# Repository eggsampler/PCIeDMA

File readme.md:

# PCIeDMA

Open source Artix-7 FPGA designed to be used with [PCILeech](https://github.com/ufrisk/pcileech/).

For schematic/layout/assembly/pcb diagrams, please see the [outputs](outputs/) folder.

## Overview

Initial design was based on a combination of the [LambdaConcept PCIe Screamer Squirrel](https://shop.lambdaconcept.com/home/50-screamer-pcie-squirrel.html) and the [Enigma-X1 LeetDMA](https://enigma-x1.com/store/product/23-leetdma-incl-custom-fw/).

PCIexpress layout is based on [lucanastasio/PCIexpress-KiCad](https://github.com/lucanastasio/PCIexpress-KiCad) PCIexpress_x4_low.

Initially will try to keep the board as a 6-layer PCB using the [JLC3313 6-Layer Impedance Control Stackup](https://cart.jlcpcb.com/impedance), layer stackup plan would be Signal/Ground/Power/Power/Ground/Signal, with the outside signal layers also having a ground pour. PCIe and USB3 SS traces would be impedance matched (and length matched as necessary) on top and bottom layers as coplanar waveguides for each pair.

There are two on-board USB-C ports, one for JTAG debugging/programming of the FPGA/flash, the other as a usb superspeed link for DMA access. The board is also designed such that it can be powered and programmed/tested from the JTAG USB connector, without needing to be plugged into a PCIe slot.

## Progress 

From a high level perspective, the board is largely complete. It does, however, need to be checked before first batch ordered. The following is a rough list of what needs to be reviewed, and any input is welcome from knowledgeable parties.

* [ ] Schematic Review
  * [ ] Part Selection
  * [ ] BOM Check
  * [ ] Connectivity

* [ ] PCB Review
  * [ ] Placement
  * [ ] Footprints
  * [ ] Routing
  * [ ] Impedance

Once board is finalised, the software side needs to be started integrating with PCILeech. Specifically, [PCILeech FPGA](https://github.com/ufrisk/pcileech-fpga)

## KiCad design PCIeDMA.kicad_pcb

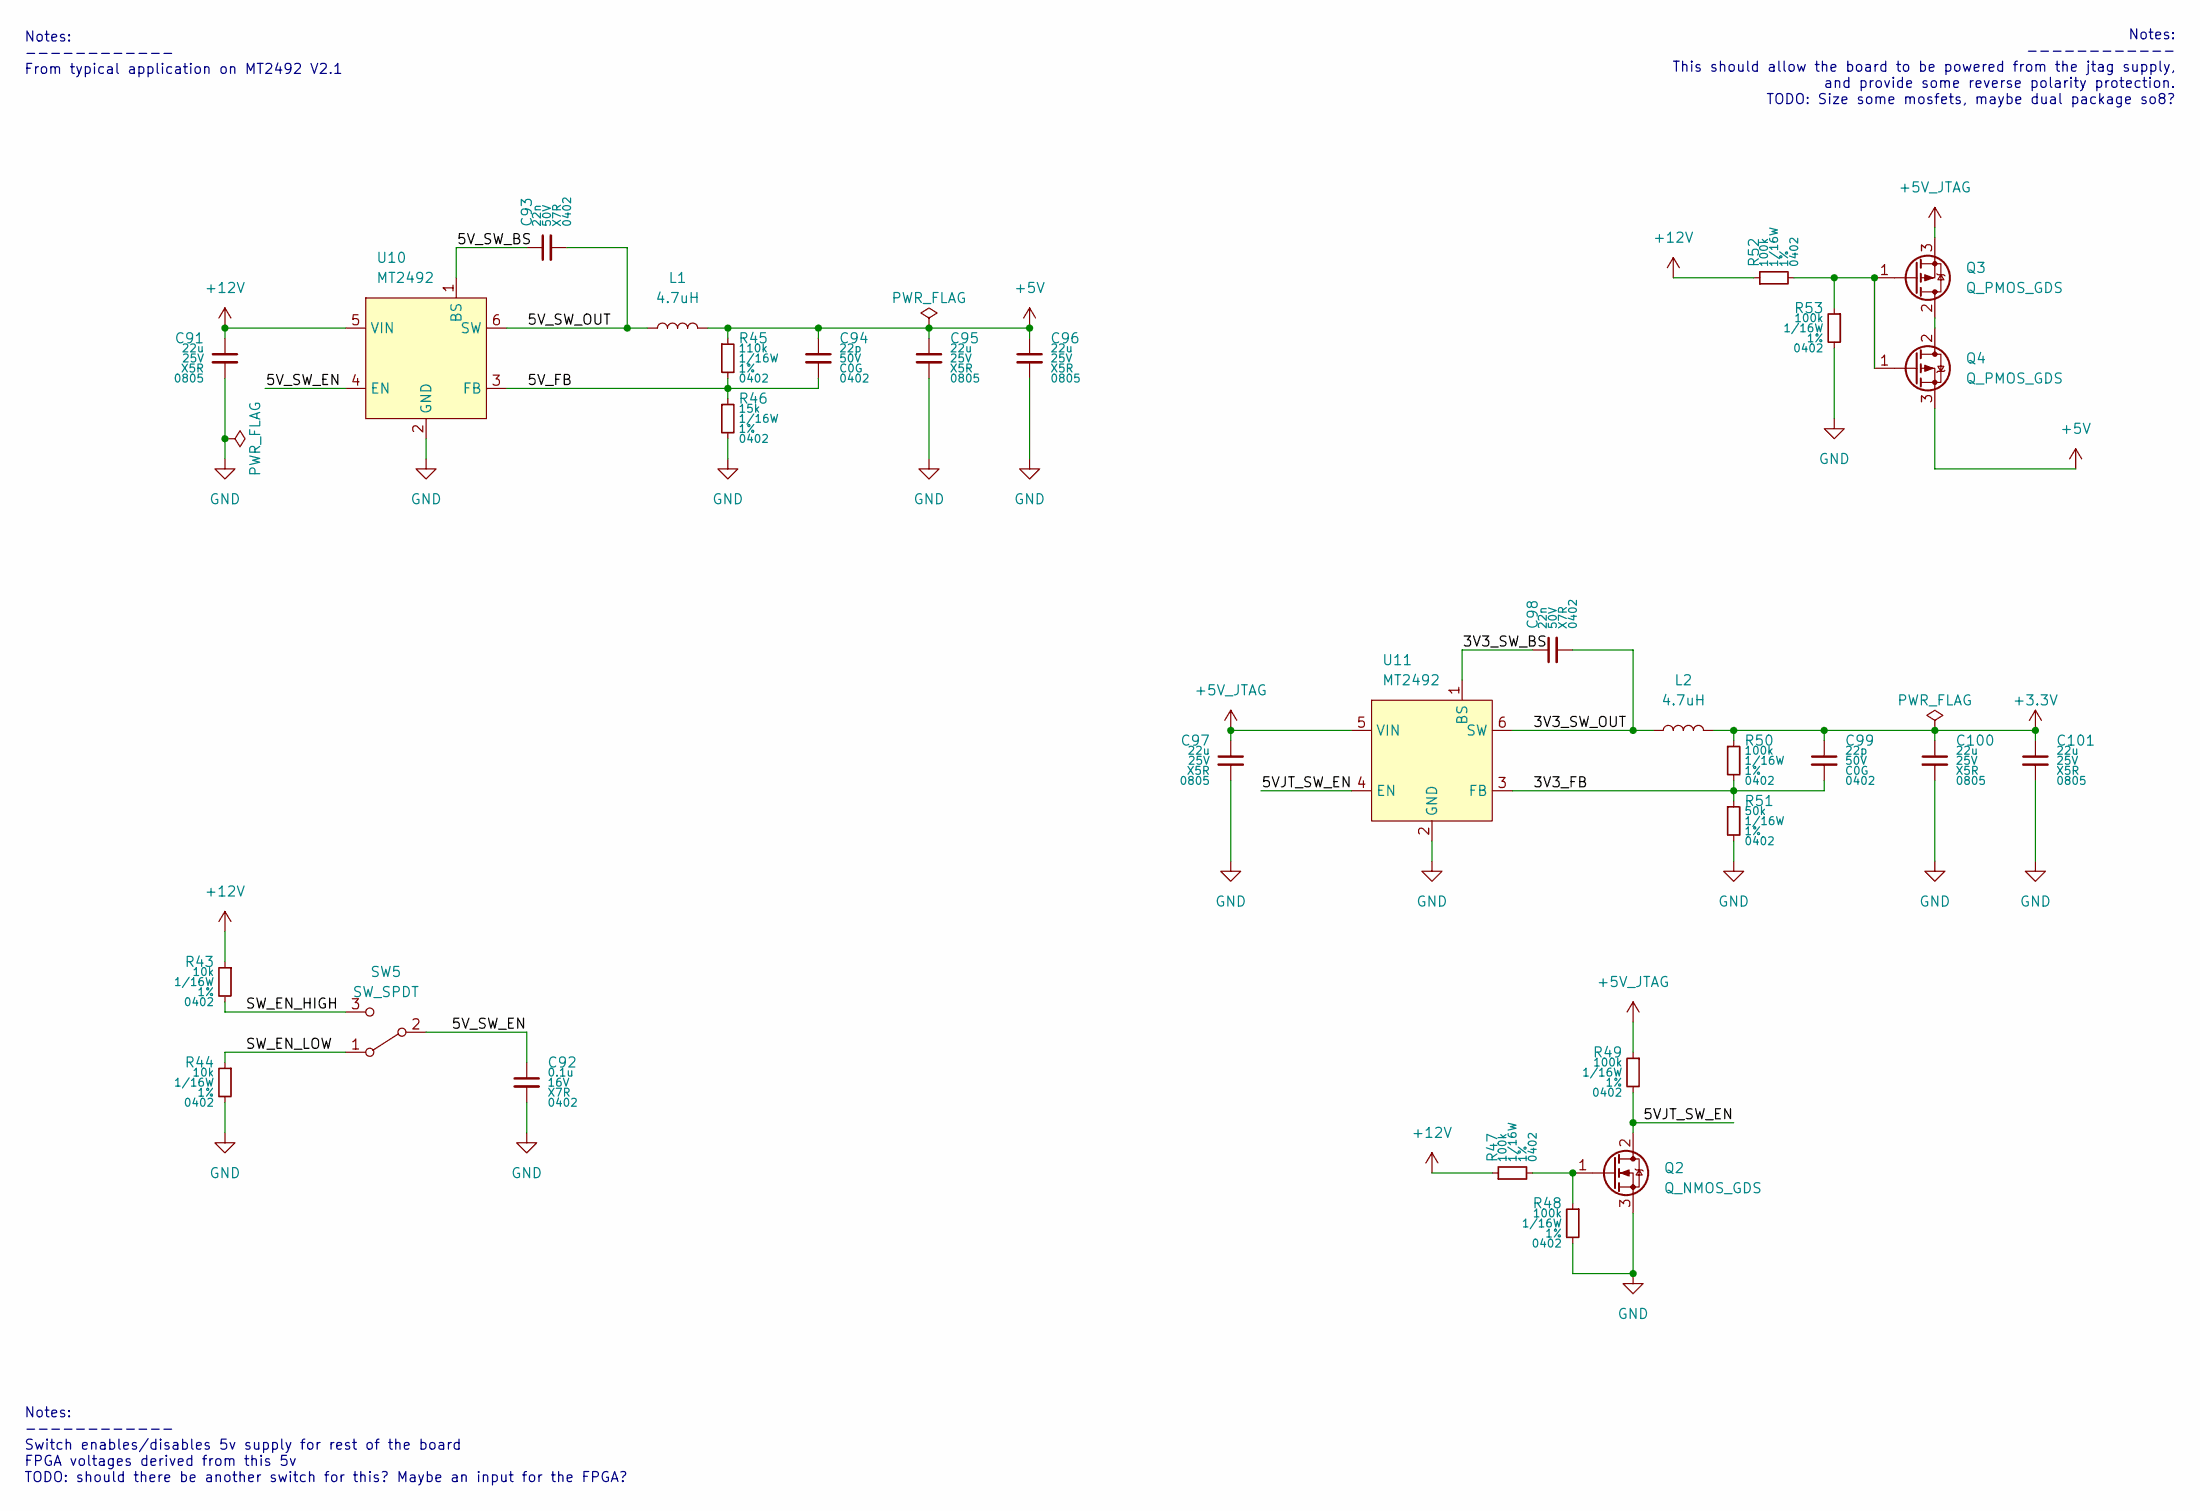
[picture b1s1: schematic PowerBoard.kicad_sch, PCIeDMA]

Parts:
C91, C95, C96, C97, C100, C101: 22u; C_0805_2012Metric; Rating 25V
C92: 0.1u; C_0402_1005Metric; Rating 16V
C93, C98: 22n; C_0402_1005Metric; Rating 50V
C94, C99: 22p; C_0402_1005Metric; Rating 50V
L1, L2: 4.7uH; L_Vishay_IHLP-2020
Q2: Q_NMOS_GDS; SOT-23
Q3, Q4: Q_PMOS_GDS; SOT-23
R43, R44: 10k; R_0402_1005Metric; Rating 1/16W; Tolerance 1%
R45: 110k; R_0402_1005Metric; Rating 1/16W; Tolerance 1%
R46: 15k; R_0402_1005Metric; Rating 1/16W; Tolerance 1%
R47, R48, R49, R50, R52, R53: 100k; R_0402_1005Metric; Rating 1/16W; Tolerance 1%
R51: 50k; R_0402_1005Metric; Rating 1/16W; Tolerance 1%
SW5: SW_SPDT; ST-0-102-C03-N003-RS
U10, U11: MT2492; SOT-23-6

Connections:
+3.3V: C99.1, C100.1, C101.1, L2.2, R50.1; also elsewhere on the board
+5V: C94.1, C95.1, C96.1, L1.2, Q4.3 (S), R45.1; also elsewhere on the board
+5V_JTAG: C97.1, Q3.3 (S), R49.1, U11.5 (VIN); also elsewhere on the board
+12V: C91.1, R43.1, R47.1, R52.1, U10.5 (VIN); also elsewhere on the board
/Board Power/3V3_FB: C99.2, R50.2, R51.1, U11.3 (FB)
/Board Power/3V3_SW_BS: C98.1, U11.1 (BS)
/Board Power/3V3_SW_OUT: C98.2, L2.1, U11.6 (SW)
/Board Power/5VJT_SW_EN: Q2.2 (D), R49.2, U11.4 (EN)
/Board Power/5V_FB: C94.2, R45.2, R46.1, U10.3 (FB)
/Board Power/5V_SW_BS: C93.1, U10.1 (BS)
/Board Power/5V_SW_EN: C92.1, SW5.2 (B), U10.4 (EN)
/Board Power/5V_SW_OUT: C93.2, L1.1, U10.6 (SW)
/Board Power/SW_EN_HIGH: R43.2, SW5.3 (C)
/Board Power/SW_EN_LOW: R44.1, SW5.1 (A)
GND: C91.2, C92.2, C95.2, C96.2, C97.2, C100.2, C101.2, Q2.3 (S), R44.2, R46.2, R48.2, R51.2, R53.2, U10.2 (GND), U11.2 (GND); also elsewhere on the board
unnamed: Q2.1 (G), R47.2, R48.1
unnamed: Q3.2 (D), Q4.2 (D)
unnamed: Q3.1 (G), Q4.1 (G), R52.2, R53.1

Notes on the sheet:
Notes: ------------ From typical application on MT2492 V2.1
Notes: ------------ Switch enables/disables 5v supply for rest of the board FPGA voltages derived from this 5v TODO: should there be another switch for this? Maybe an input for the FPGA?
Notes: ------------ This should allow the board to be powered from the jtag supply, and provide some reverse polarity protection. TODO: Size some mosfets, maybe dual package so8?

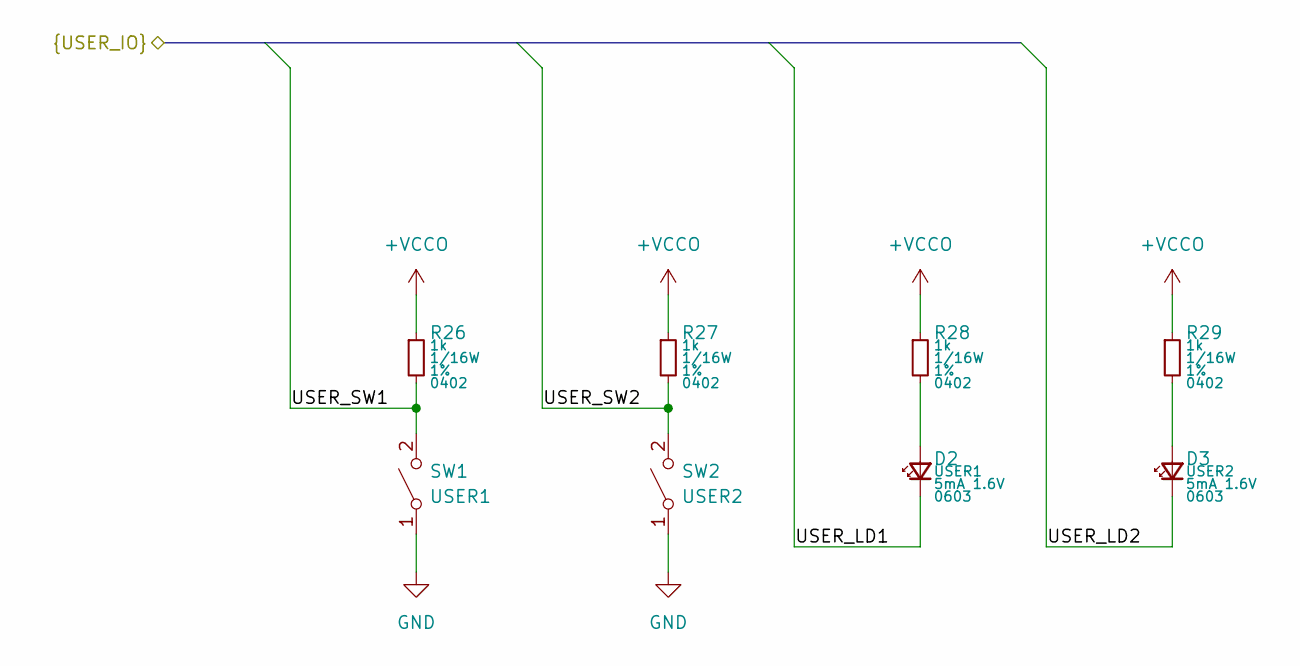
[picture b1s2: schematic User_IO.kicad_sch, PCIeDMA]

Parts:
D2: USER1; LED_0603_1608Metric; Rating 5mA 1.6V
D3: USER2; LED_0603_1608Metric; Rating 5mA 1.6V
R26, R27, R28, R29: 1k; R_0402_1005Metric; Rating 1/16W; Tolerance 1%
SW1: USER1; SW_SPST_B3U-1000P
SW2: USER2; SW_SPST_B3U-1000P

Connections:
+VCCO: R26.1, R27.1, R28.1, R29.1; also elsewhere on the board
/FPGA/USER_LD1: D2.1 (K); also elsewhere on the board
/FPGA/USER_LD2: D3.1 (K); also elsewhere on the board
/FPGA/USER_SW1: R26.2, SW1.2 (B); also elsewhere on the board
/FPGA/USER_SW2: R27.2, SW2.2 (B); also elsewhere on the board
GND: SW1.1 (A), SW2.1 (A); also elsewhere on the board
unnamed: D2.2 (A), R28.2
unnamed: D3.2 (A), R29.2

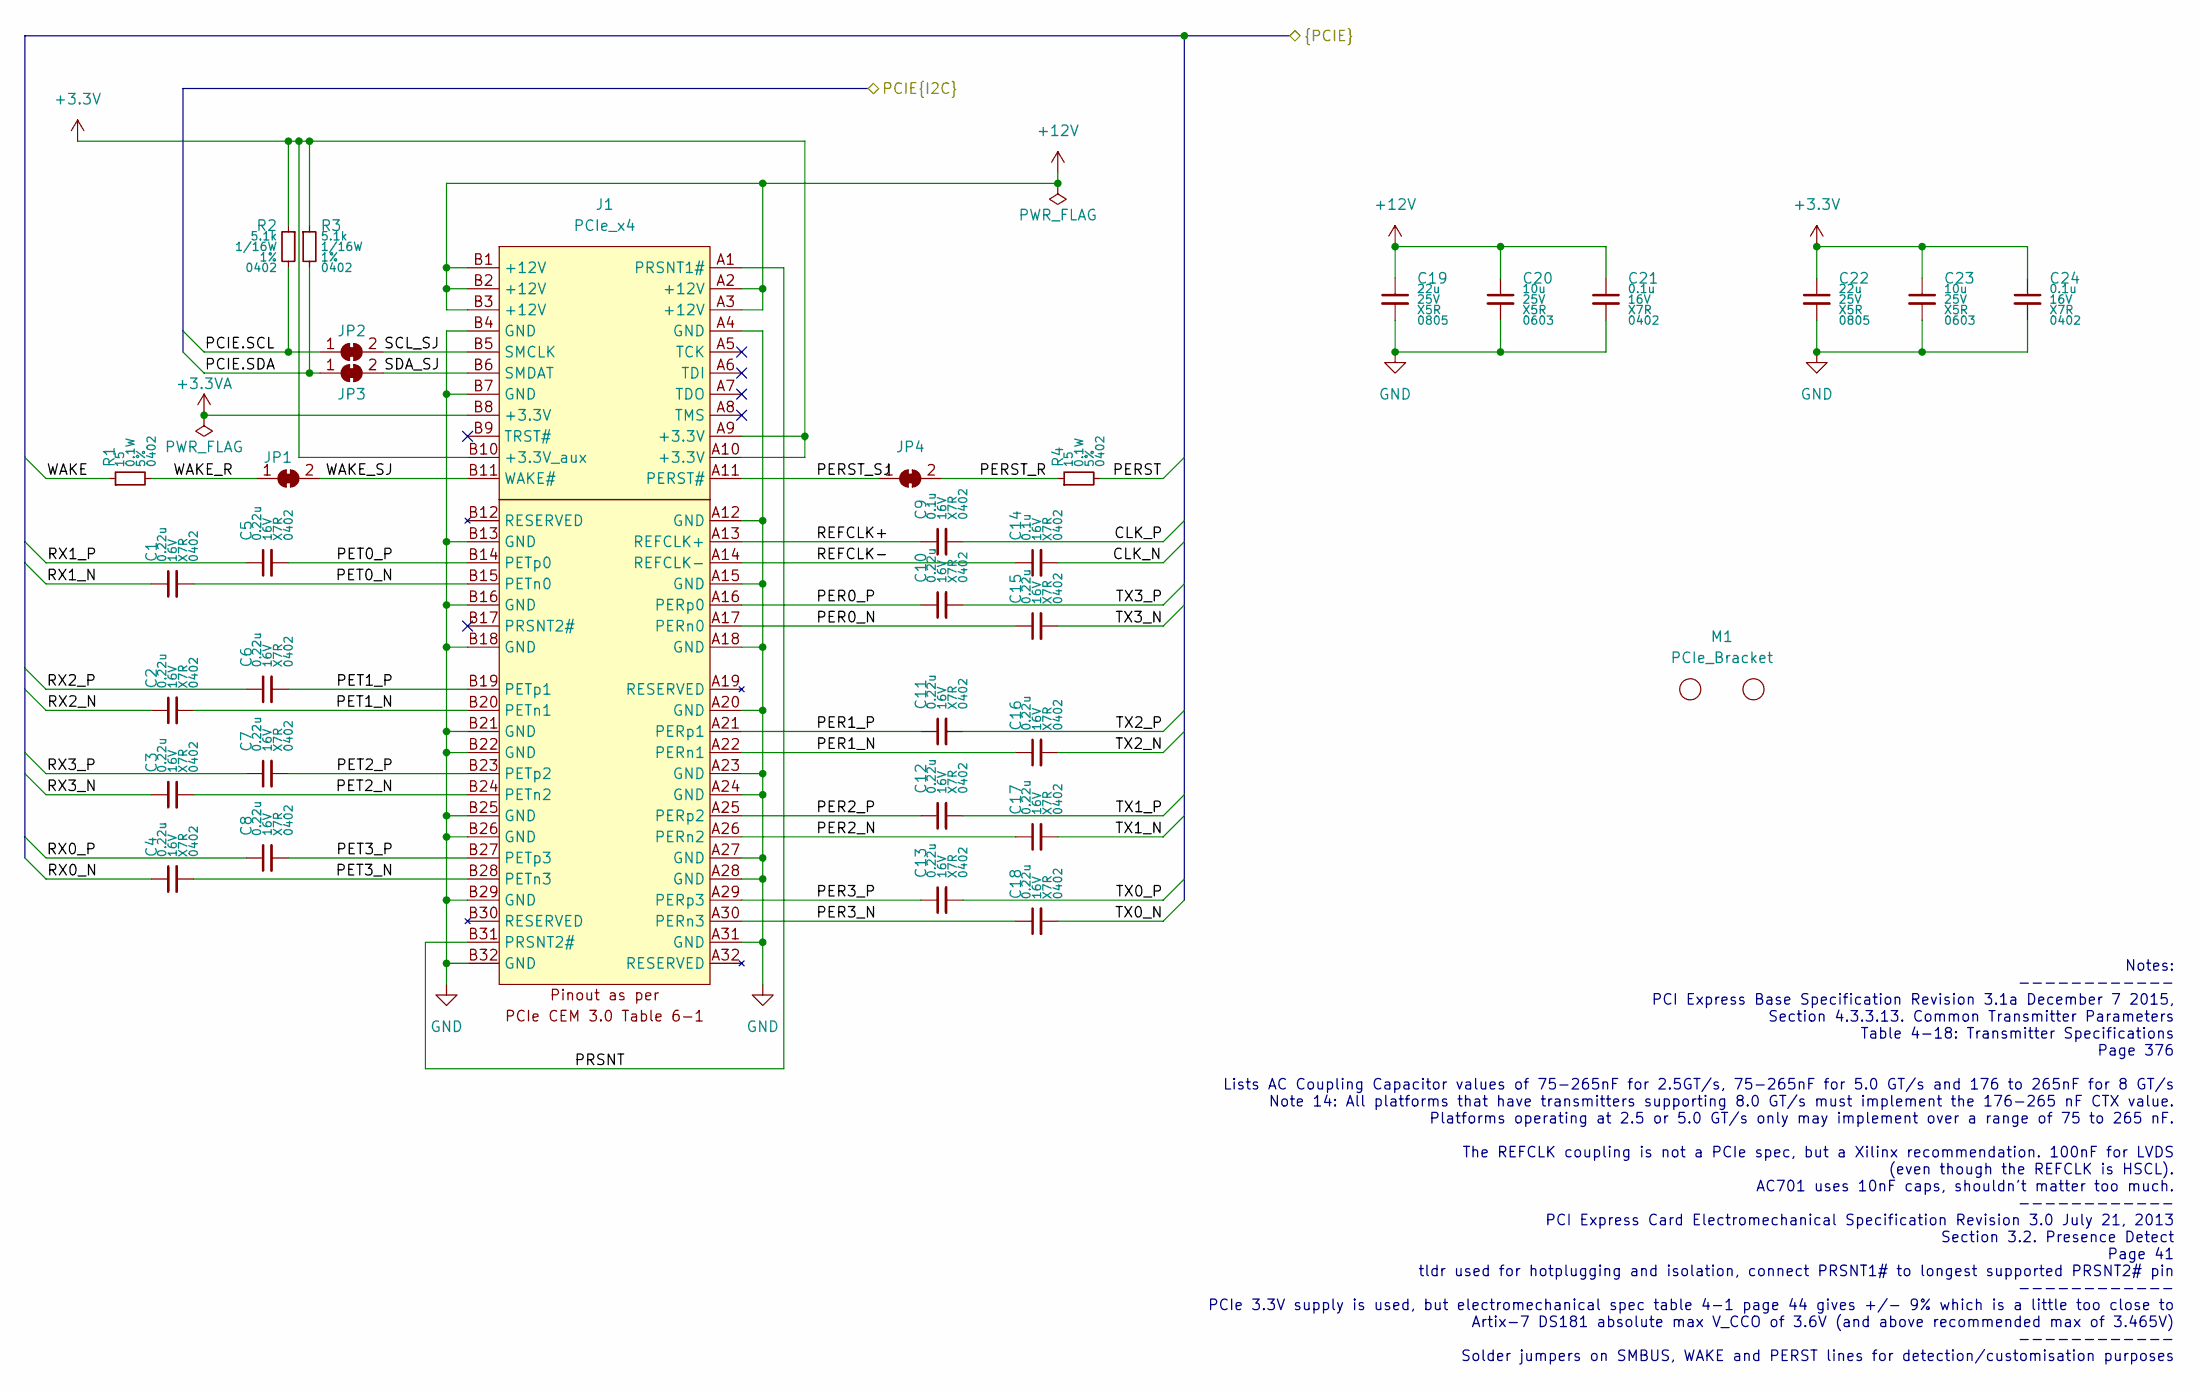
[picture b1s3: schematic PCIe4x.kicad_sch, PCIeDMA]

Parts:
C1, C2, C3, C4, C5, C6, C7, C8, C10, C11, C12, C13, C15, C16, C17, C18: 0.22u; C_0402_1005Metric; Rating 16V
C9, C14, C21, C24: 0.1u; C_0402_1005Metric; Rating 16V
C19, C22: 22u; C_0805_2012Metric; Rating 25V
C20, C23: 10u; C_0603_1608Metric; Rating 25V
J1: PCIe_x4; BUS_PCIexpress_x4
JP1, JP2, JP3, JP4: SolderJumper_2_Bridged; SolderJumper-2_P1.3mm_Bridged_RoundedPad1.0x1.5mm
M1: PCIe_Bracket
R1, R4: 15; R_0402_1005Metric; Rating 0.1W; Tolerance 5%
R2, R3: 5.1k; R_0402_1005Metric; Rating 1/16W; Tolerance 1%

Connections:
+3.3V: C22.1, C23.1, C24.1, J1.A9 (+3.3V), J1.A10 (+3.3V), J1.B10 (+3.3V_aux), R2.1, R3.1; also elsewhere on the board
+3.3VA: J1.B8 (+3.3V)
+12V: C19.1, C20.1, C21.1, J1.A2 (+12V), J1.A3 (+12V), J1.B1 (+12V), J1.B2 (+12V), J1.B3 (+12V); also elsewhere on the board
/FPGA/CLK_N: C14.2; also elsewhere on the board
/FPGA/CLK_P: C9.2; also elsewhere on the board
/FPGA/PCIE.SCL: JP2.1 (A), R2.2; also elsewhere on the board
/FPGA/PCIE.SDA: JP3.1 (A), R3.2; also elsewhere on the board
/FPGA/PERST: R4.2; also elsewhere on the board
/FPGA/RX0_N: C4.1; also elsewhere on the board
/FPGA/RX0_P: C8.1; also elsewhere on the board
/FPGA/RX1_N: C1.1; also elsewhere on the board
/FPGA/RX1_P: C5.1; also elsewhere on the board
/FPGA/RX2_N: C2.1; also elsewhere on the board
/FPGA/RX2_P: C6.1; also elsewhere on the board
/FPGA/RX3_N: C3.1; also elsewhere on the board
/FPGA/RX3_P: C7.1; also elsewhere on the board
/FPGA/TX0_N: C18.2; also elsewhere on the board
/FPGA/TX0_P: C13.2; also elsewhere on the board
/FPGA/TX1_N: C17.2; also elsewhere on the board
/FPGA/TX1_P: C12.2; also elsewhere on the board
/FPGA/TX2_N: C16.2; also elsewhere on the board
/FPGA/TX2_P: C11.2; also elsewhere on the board
/FPGA/TX3_N: C15.2; also elsewhere on the board
/FPGA/TX3_P: C10.2; also elsewhere on the board
/FPGA/WAKE: R1.1; also elsewhere on the board
/PCIe 4x/PER0_N: C15.1, J1.A17 (PERn0)
/PCIe 4x/PER0_P: C10.1, J1.A16 (PERp0)
/PCIe 4x/PER1_N: C16.1, J1.A22 (PERn1)
/PCIe 4x/PER1_P: C11.1, J1.A21 (PERp1)
/PCIe 4x/PER2_N: C17.1, J1.A26 (PERn2)
/PCIe 4x/PER2_P: C12.1, J1.A25 (PERp2)
/PCIe 4x/PER3_N: C18.1, J1.A30 (PERn3)
/PCIe 4x/PER3_P: C13.1, J1.A29 (PERp3)
/PCIe 4x/PERST_R: JP4.2 (B), R4.1
/PCIe 4x/PERST_SJ: J1.A11 (PERST#), JP4.1 (A)
/PCIe 4x/PET0_N: C1.2, J1.B15 (PETn0)
/PCIe 4x/PET0_P: C5.2, J1.B14 (PETp0)
/PCIe 4x/PET1_N: C2.2, J1.B20 (PETn1)
/PCIe 4x/PET1_P: C6.2, J1.B19 (PETp1)
/PCIe 4x/PET2_N: C3.2, J1.B24 (PETn2)
/PCIe 4x/PET2_P: C7.2, J1.B23 (PETp2)
/PCIe 4x/PET3_N: C4.2, J1.B28 (PETn3)
/PCIe 4x/PET3_P: C8.2, J1.B27 (PETp3)
/PCIe 4x/PRSNT: J1.A1 (PRSNT1#), J1.B31 (PRSNT2#)
/PCIe 4x/REFCLK+: C9.1, J1.A13 (REFCLK+)
/PCIe 4x/REFCLK-: C14.1, J1.A14 (REFCLK-)
/PCIe 4x/SCL_SJ: J1.B5 (SMCLK), JP2.2 (B)
/PCIe 4x/SDA_SJ: J1.B6 (SMDAT), JP3.2 (B)
/PCIe 4x/WAKE_R: JP1.1 (A), R1.2
/PCIe 4x/WAKE_SJ: J1.B11 (WAKE#), JP1.2 (B)
GND: C19.2, C20.2, C21.2, C22.2, C23.2, C24.2, J1.A4 (GND), J1.A12 (GND), J1.A15 (GND), J1.A18 (GND), J1.A20 (GND), J1.A23 (GND), J1.A24 (GND), J1.A27 (GND), J1.A28 (GND), J1.A31 (GND), J1.B4 (GND), J1.B7 (GND), J1.B13 (GND), J1.B16 (GND), J1.B18 (GND), J1.B21 (GND), J1.B22 (GND), J1.B25 (GND), J1.B26 (GND), J1.B29 (GND), J1.B32 (GND); also elsewhere on the board

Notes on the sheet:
Notes: ------------ PCI Express Base Specification Revision 3.1a December 7 2015, Section 4.3.3.13. Common Transmitter Parameters Table 4-18: Transmitter Specifications Page 376 Lists AC Coupling Capacitor values of 75-265nF for 2.5GT/s, 75-265nF for 5.0 GT/s and 176 to 265nF for 8 GT/s Note 14: Al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

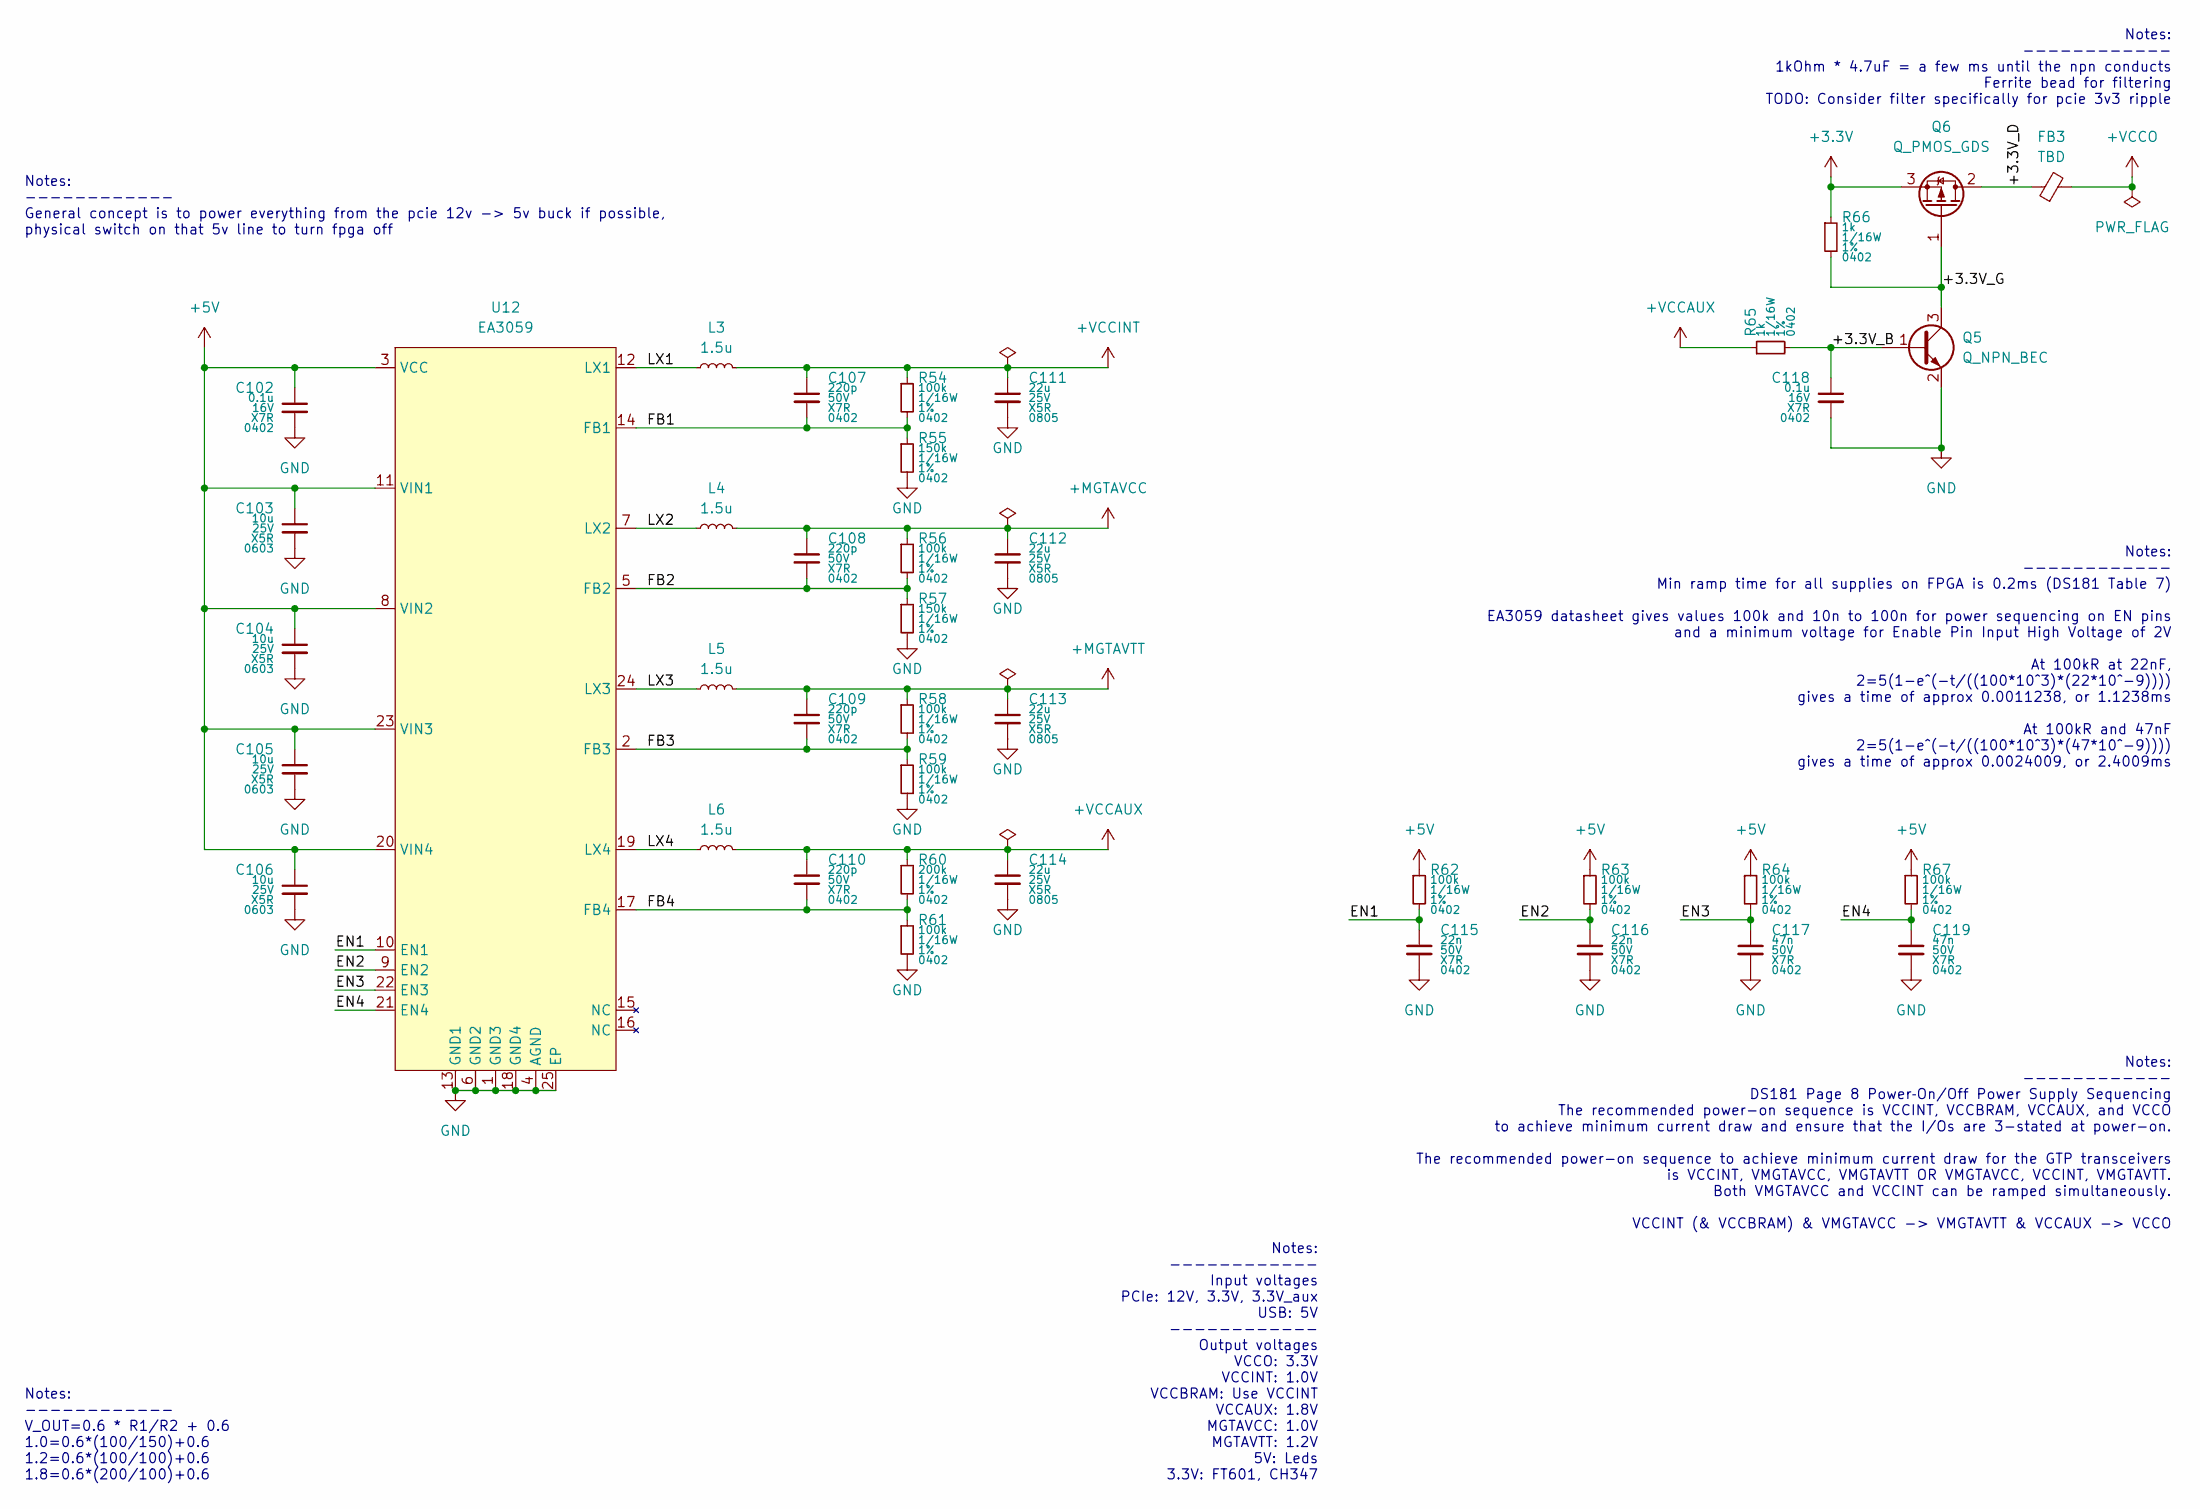
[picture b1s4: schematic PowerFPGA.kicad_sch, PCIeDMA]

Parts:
C102, C118: 0.1u; C_0402_1005Metric; Rating 16V
C103, C104, C105, C106: 10u; C_0603_1608Metric; Rating 25V
C107, C108, C109, C110: 220p; C_0402_1005Metric; Rating 50V
C111, C112, C113, C114: 22u; C_0805_2012Metric; Rating 25V
C115, C116: 22n; C_0402_1005Metric; Rating 50V
C117, C119: 47n; C_0402_1005Metric; Rating 50V
FB3: TBD; L_0805_2012Metric
L3, L4, L5, L6: 1.5u; L_Abracon_ASPI-3012S
Q5: Q_NPN_BEC; SOT-23
Q6: Q_PMOS_GDS; SOT-23
R54, R56, R58, R59, R61, R62, R63, R64, R67: 100k; R_0402_1005Metric; Rating 1/16W; Tolerance 1%
R55, R57: 150k; R_0402_1005Metric; Rating 1/16W; Tolerance 1%
R60: 200k; R_0402_1005Metric; Rating 1/16W; Tolerance 1%
R65, R66: 1k; R_0402_1005Metric; Rating 1/16W; Tolerance 1%
U12: EA3059; QFN-24-1EP_4x4mm_P0.5mm_EP2.6x2.6mm

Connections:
+3.3V: Q6.3 (S), R66.1; also elsewhere on the board
+5V: C102.1, C103.1, C104.1, C105.1, C106.1, R62.1, R63.1, R64.1, R67.1, U12.3 (VCC), U12.8 (VIN2), U12.11 (VIN1), U12.20 (VIN4), U12.23 (VIN3); also elsewhere on the board
+MGTAVCC: C108.1, C112.1, L4.2, R56.1; also elsewhere on the board
+MGTAVTT: C109.1, C113.1, L5.2, R58.1; also elsewhere on the board
+VCCAUX: C110.1, C114.1, L6.2, R60.1, R65.1; also elsewhere on the board
+VCCINT: C107.1, C111.1, L3.2, R54.1; also elsewhere on the board
+VCCO: FB3.2; also elsewhere on the board
/FPGA Power/+3.3V_B: C118.1, Q5.1 (B), R65.2
/FPGA Power/+3.3V_D: FB3.1, Q6.2 (D)
/FPGA Power/+3.3V_G: Q5.3 (C), Q6.1 (G), R66.2
/FPGA Power/EN1: C115.1, R62.2, U12.10 (EN1)
/FPGA Power/EN2: C116.1, R63.2, U12.9 (EN2)
/FPGA Power/EN3: C117.1, R64.2, U12.22 (EN3)
/FPGA Power/EN4: C119.1, R67.2, U12.21 (EN4)
/FPGA Power/FB1: C107.2, R54.2, R55.1, U12.14 (FB1)
/FPGA Power/FB2: C108.2, R56.2, R57.1, U12.5 (FB2)
/FPGA Power/FB3: C109.2, R58.2, R59.1, U12.2 (FB3)
/FPGA Power/FB4: C110.2, R60.2, R61.1, U12.17 (FB4)
/FPGA Power/LX1: L3.1, U12.12 (LX1)
/FPGA Power/LX2: L4.1, U12.7 (LX2)
/FPGA Power/LX3: L5.1, U12.24 (LX3)
/FPGA Power/LX4: L6.1, U12.19 (LX4)
GND: C102.2, C103.2, C104.2, C105.2, C106.2, C111.2, C112.2, C113.2, C114.2, C115.2, C116.2, C117.2, C118.2, C119.2, Q5.2 (E), R55.2, R57.2, R59.2, R61.2, U12.1 (GND3), U12.4 (AGND), U12.6 (GND2), U12.13 (GND1), U12.18 (GND4), U12.25 (EP); also elsewhere on the board

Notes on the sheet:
Notes: ------------ V_OUT=0.6 * R1/R2 + 0.6 1.0=0.6*(100/150)+0.6 1.2=0.6*(100/100)+0.6 1.8=0.6*(200/100)+0.6
Notes: ------------ General concept is to power everything from the pcie 12v -> 5v buck if possible, physical switch on that 5v line to turn fpga off
Notes: ------------ 1kOhm * 4.7uF = a few ms until the npn conducts Ferrite bead for filtering TODO: Consider filter specifically for pcie 3v3 ripple
Notes: ------------ DS181 Page 8 Power‐On/Off Power Supply Sequencing The recommended power-on sequence is VCCINT, VCCBRAM, VCCAUX, and VCCO to achieve minimum current draw and ensure that the I/Os are 3-stated at power-on. The recommended power-on sequence to achieve minimum current draw for the G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
Notes: ------------ Min ramp time for all supplies on FPGA is 0.2ms (DS181 Table 7) EA3059 datasheet gives values 100k and 10n to 100n for power sequencing on EN pins and a minimum voltage for Enable Pin Input High Voltage of 2V At 100kR at 22nF, 2=5(1-e^(-t/((100*10^3)*(22*10^-9)))) gives a time o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
Notes: ------------ Input voltages PCIe: 12V, 3.3V, 3.3V_aux USB: 5V ------------ Output voltages VCCO: 3.3V VCCINT: 1.0V VCCBRAM: Use VCCINT VCCAUX: 1.8V MGTAVCC: 1.0V MGTAVTT: 1.2V 5V: Leds 3.3V: FT601, CH347

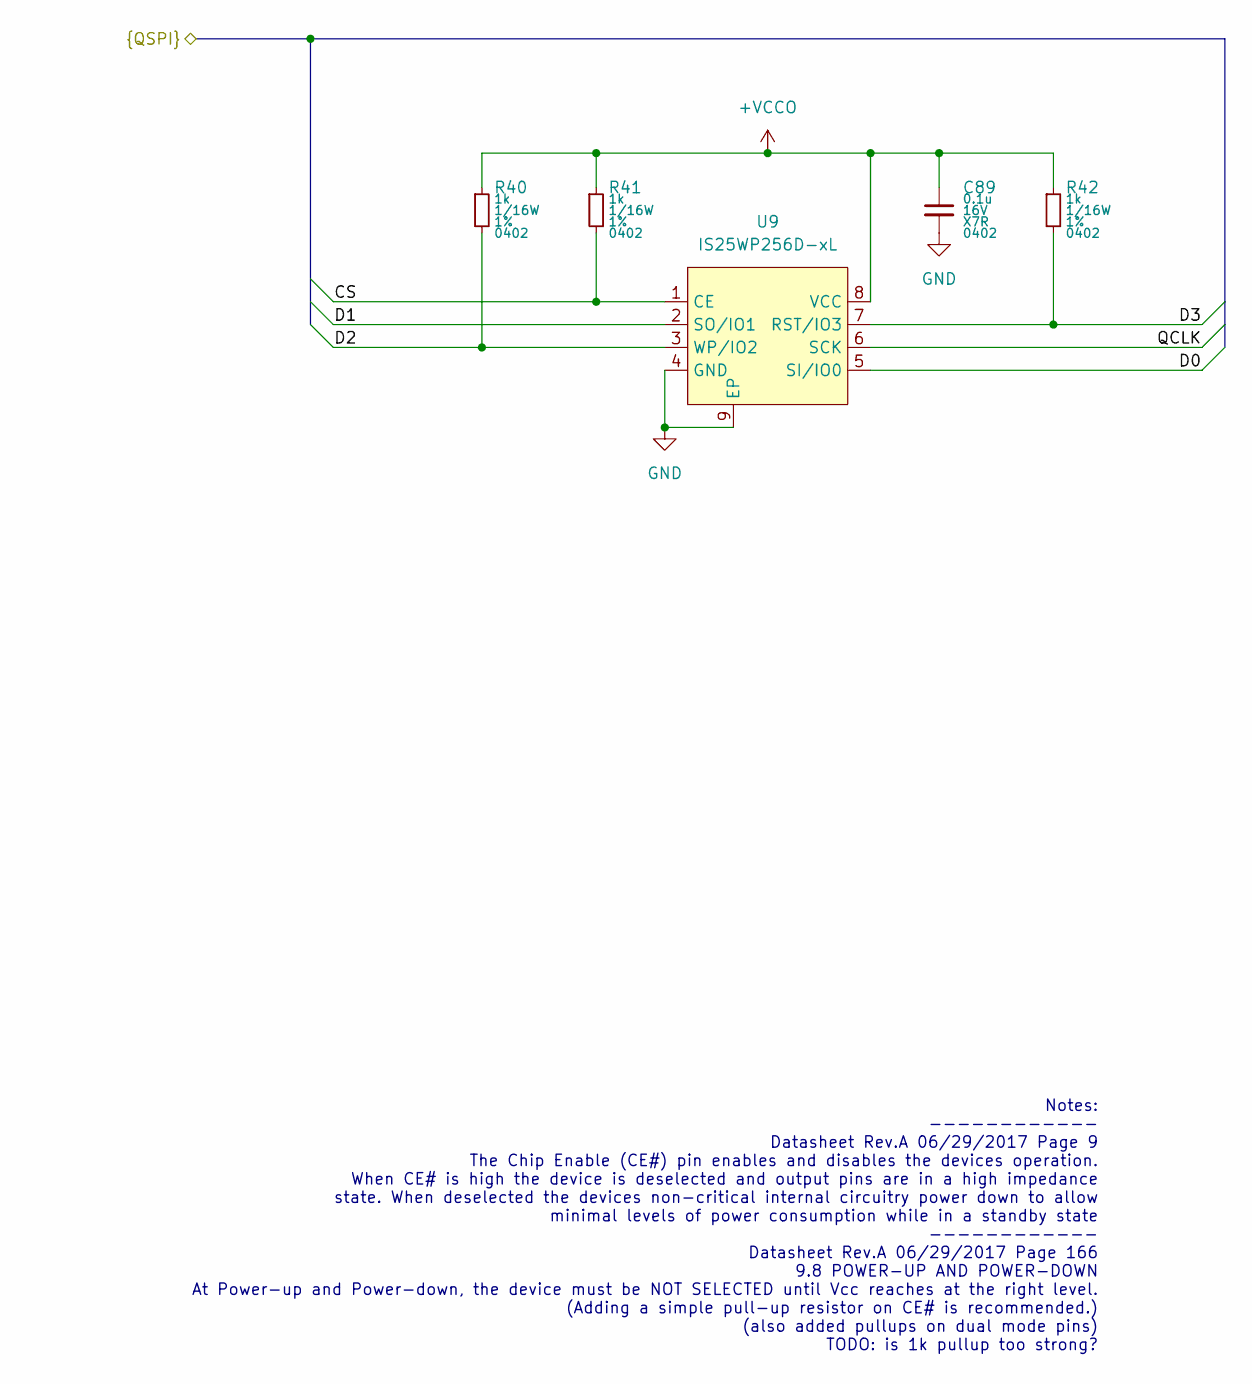
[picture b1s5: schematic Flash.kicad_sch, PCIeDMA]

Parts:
C89: 0.1u; C_0402_1005Metric; Rating 16V
R40, R41, R42: 1k; R_0402_1005Metric; Rating 1/16W; Tolerance 1%
U9: IS25WP256D-xL; WSON-8-1EP_8x6mm_P1.27mm_EP3.4x4.3mm

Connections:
+VCCO: C89.1, R40.1, R41.1, R42.1, U9.8 (VCC); also elsewhere on the board
/FPGA/CS: R41.2, U9.1 (CE); also elsewhere on the board
/FPGA/D0: U9.5 (SI/IO0); also elsewhere on the board
/FPGA/D1: U9.2 (SO/IO1); also elsewhere on the board
/FPGA/D2: R40.2, U9.3 (WP/IO2); also elsewhere on the board
/FPGA/D3: R42.2, U9.7 (RST/IO3); also elsewhere on the board
/FPGA/QCLK: U9.6 (SCK); also elsewhere on the board
GND: C89.2, U9.4 (GND), U9.9 (EP); also elsewhere on the board

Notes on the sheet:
Notes: ------------ Datasheet Rev.A 06/29/2017 Page 9 The Chip Enable (CE#) pin enables and disables the devices operation. When CE# is high the device is deselected and output pins are in a high impedance state. When deselected the devices non-critical internal circuitry power down to allow minima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
